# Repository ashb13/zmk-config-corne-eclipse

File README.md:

README | [Keymap](KEYMAP.md) | [MX Parts](PARTS_MX.md) | [Building](BUILDING.md) | [Tricks](TRICKS.md)

# Corne Eclipse

---

The Corne Eclipse is a highly customized wireless Corne MX.

*This was a project I initially finished in 2021. Finally updated and open sourced!*

## Custom Circuit Board Design

- JST port with line passthrough for undercarriage battery storage
- Native support for dual nice!view displays
- Native support for dual Alps EC11/EC12 encoders
- Native support for heftier side mounted power switches
- Native support for tenting puck

## Custom Shield Casing Design

Based on Void's case.

- Undercarriage battery storage
- Optimized material usage for bottom
- Native support for tenting puck

## Peripheral-side Trackpad Support

- TPS43 (and related Azoteq IQS5xx modules) via [AYM1607/zmk-driver-azoteq-iqs5xx](https://github.com/AYM1607/zmk-driver-azoteq-iqs5xx)
- Cirque Touchpad via [petejohanson/cirque-input-module](https://github.com/petejohanson/cirque-input-module)

## ZMK Modifications

### External Display Upgrades

- Lithium curve LUT applied for a 403450 to get more accurate numeric charge data (PR reference: [ZMK PR 2066](https://github.com/zmkfirmware/zmk/pull/2066))
- Track battery status of both halves on a single nice!view
- Capslock indicator

### RGB Battery Optimizations

Powered by [zmk-ext-power-smart-idle](https://github.com/Frosthaven/zmk-ext-power-smart-idle).

- 20% brightness when not plugged in
- RGB auto-off on low battery when not plugged in
- Lights stay on when plugged in
- Eclipse v3 reversible variant uses a MOSFET that prevents drain when LEDs are off (coming soon)

## Default Typing Layouts

Available in [releases](https://github.com/ashb13/zmk-config-corne-eclipse/releases).

- QWERTY
- Colemak Mod DH (personal choice!)
- Colemak
- Workman
- DVORAK

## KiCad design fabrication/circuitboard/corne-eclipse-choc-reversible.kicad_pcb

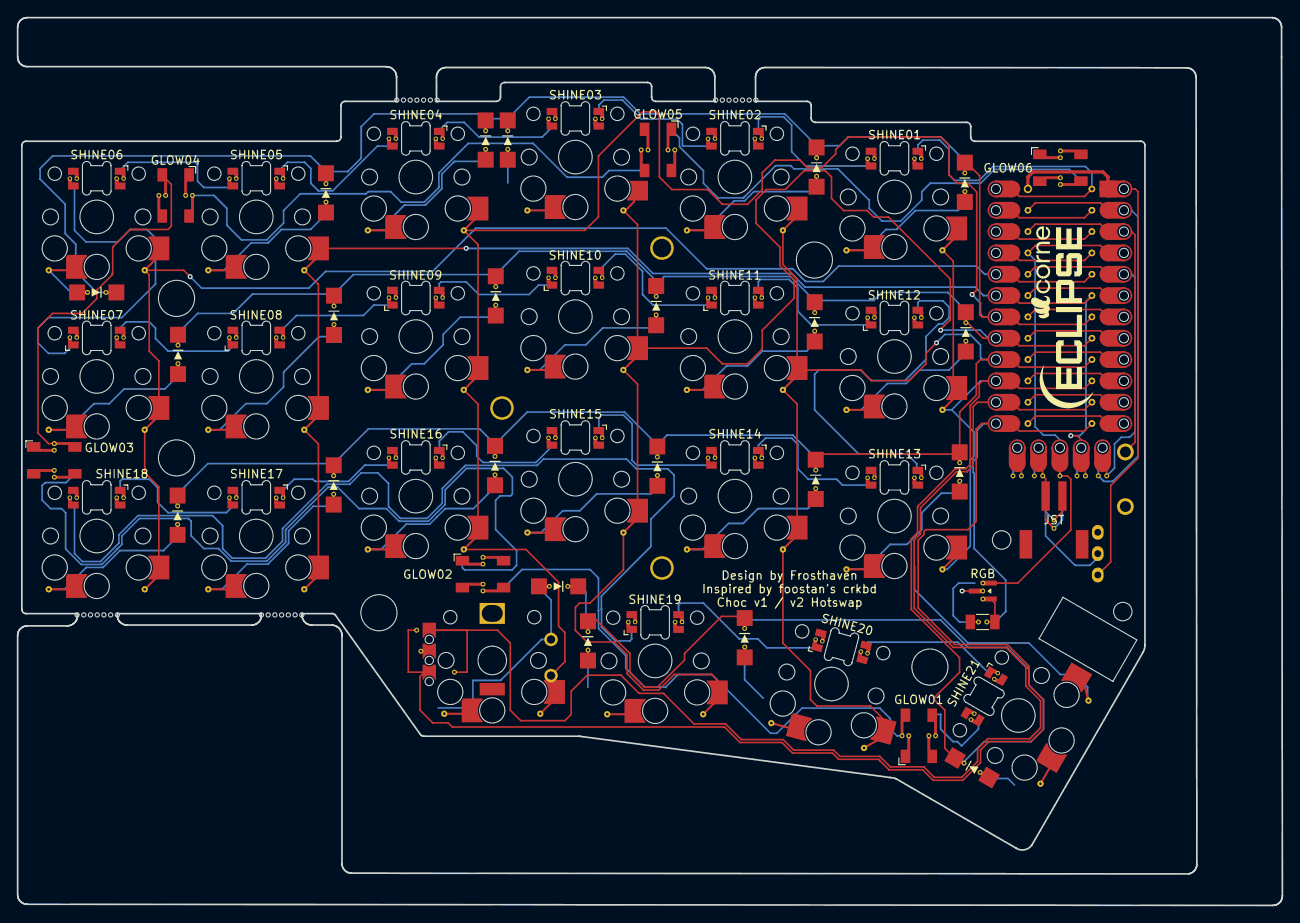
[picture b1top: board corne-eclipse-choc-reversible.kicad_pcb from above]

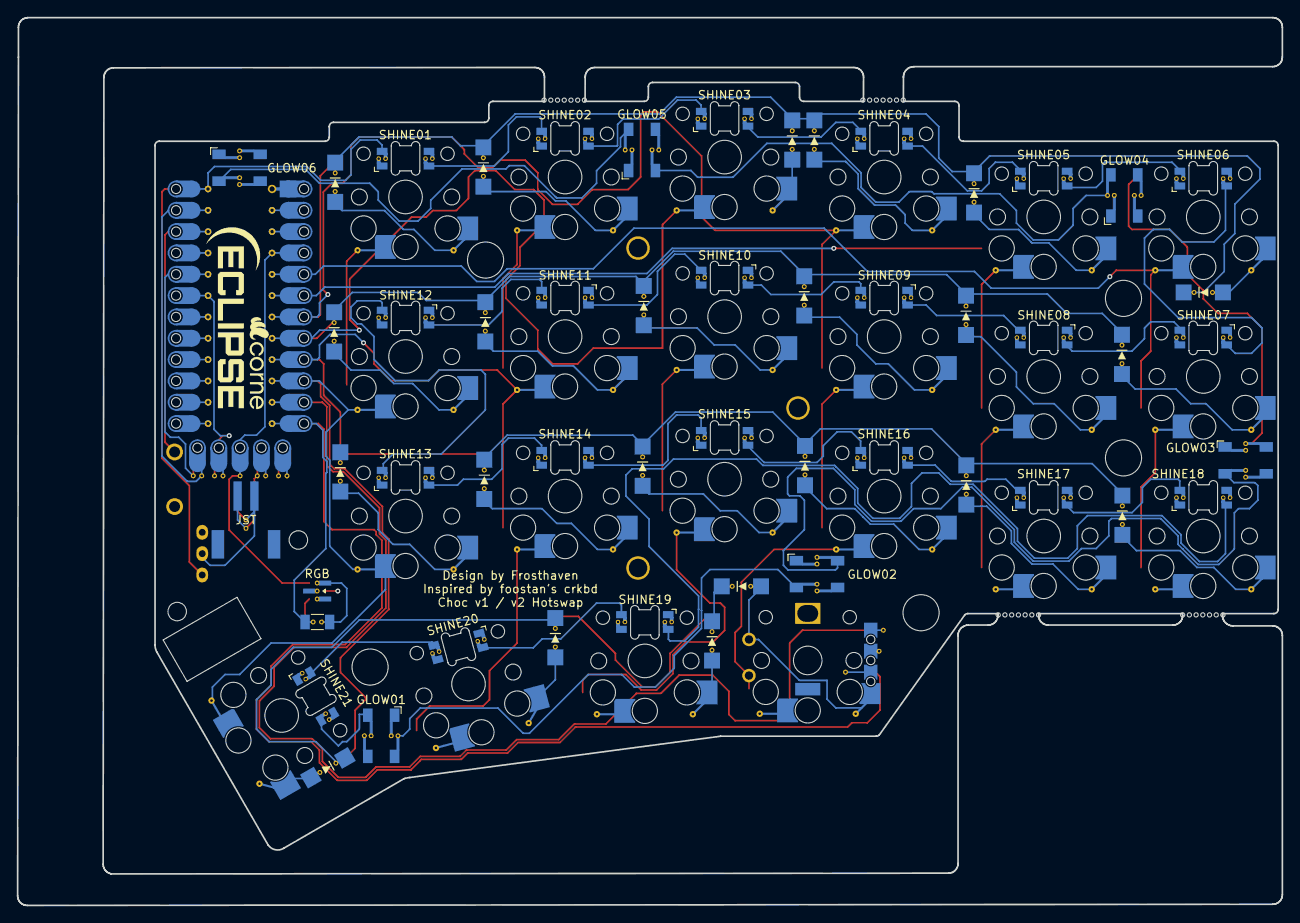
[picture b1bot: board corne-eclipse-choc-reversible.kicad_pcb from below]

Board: 4 copper layers, 150.6 x 105.7 mm, 91 parts (51 on the bottom side), 71 nets.

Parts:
BT1, BT2, BT3, BT4: Breakaway_Tabs
D1, D2, D3, D4, D5, D6, D7, D8, D9, D10, D11, D12, D13, D14, D15, D16, D17, D18, D19, D19B, D20, D21: D; ComboDiode-reversible
ENC1: ENC_SW_EC12_Choc; ENC_SW_EC12_Choc-reversible
GLOW01, GLOW02, GLOW03, GLOW04, GLOW05, GLOW06: WS2812B; SK6812_5050-reversible
J2: OLED; niceview-reversible
JPT1: JST Passthrough
JST: JST_PH-reversible
MH1, MH2, MH3, MH4, MH5, MH10, MH11: Val**; M2_HOLE_v2
PWR1: PowerSW-reversible
R1: 10k; R_1206-reversible
RGBMOS: AO3401A; SOT-23-reversible
RSW1: SW_PUSH; ResetSW-reversible
SHINE01, SHINE02, SHINE03, SHINE04, SHINE05, SHINE06, SHINE07, SHINE08, SHINE09, SHINE10, SHINE11, SHINE12, SHINE13, SHINE14, SHINE15, SHINE16, SHINE17, SHINE18, SHINE19, SHINE20, SHINE21: LED_6028R; SK6812_mini_e-reversible
SW1, SW2, SW3, SW4, SW5, SW6, SW7, SW8, SW9, SW10, SW11, SW12, SW13, SW14, SW15, SW16, SW17, SW18, SW20, SW21, SW22: SW_Choc_v1v2_HS; Choc_Hotswap-reversible
TP2: Tenting Puck; Tenting_Puck-reversible
U1: nice!nano; ProMicro-reversible

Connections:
BAT+: JST.2, PWR1.2
COL0: SW1.1, SW7.1, SW13.1, U1.20
COL1: SW2.1, SW8.1, SW14.1, U1.19
COL2: ENC1.1, ENC1.S2, SW3.1, SW9.1, SW15.1, U1.18
COL3: SW4.1, SW10.1, SW16.1, SW20.1, U1.17
COL4: SW5.1, SW11.1, SW17.1, SW21.1, U1.16
COL5: SW6.1, SW12.1, SW18.1, SW22.1, U1.15
ENC_A: ENC1.B, U1.11
ENC_B: ENC1.A, U1.12
EXT_PWR: R1.1, RGBMOS.2, U1.13
GND: ENC1.C, GLOW01.3, GLOW02.3, GLOW03.3, GLOW04.3, GLOW05.3, GLOW06.3, J2.4, JST.1, RSW1.2, SHINE01.3, SHINE02.3, SHINE03.3, SHINE04.3, SHINE05.3, SHINE06.3, SHINE07.3, SHINE08.3, SHINE09.3, SHINE10.3, SHINE11.3, SHINE12.3, SHINE13.3, SHINE14.3, SHINE15.3, SHINE16.3, SHINE17.3, SHINE18.3, SHINE19.3, SHINE20.3, SHINE21.3, TP2.1, U1.3, U1.4, U1.23
LED_CHAIN: SHINE01.4, U1.1
LED_PWR: GLOW01.1, GLOW02.1, GLOW03.1, GLOW04.1, GLOW05.1, GLOW06.1, RGBMOS.3, SHINE01.1, SHINE02.1, SHINE03.1, SHINE04.1, SHINE05.1, SHINE06.1, SHINE07.1, SHINE08.1, SHINE09.1, SHINE10.1, SHINE11.1, SHINE12.1, SHINE13.1, SHINE14.1, SHINE15.1, SHINE16.1, SHINE17.1, SHINE18.1, SHINE19.1, SHINE20.1, SHINE21.1
unnamed: D1.2, SW1.2
unnamed: D2.2, SW2.2
unnamed: D3.2, SW3.2
unnamed: D4.2, SW4.2
unnamed: D5.2, SW5.2
unnamed: D6.2, SW6.2
unnamed: D7.2, SW7.2
unnamed: D8.2, SW8.2
unnamed: D9.2, SW9.2
unnamed: D10.2, SW10.2
unnamed: D11.2, SW11.2
unnamed: D12.2, SW12.2
unnamed: D13.2, SW13.2
unnamed: D14.2, SW14.2
unnamed: D15.2, SW15.2
unnamed: D16.2, SW16.2
unnamed: D17.2, SW17.2
unnamed: D18.2, SW18.2
unnamed: D19B.2, ENC1.2, ENC1.S1
unnamed: D19.2, SW20.2
unnamed: D20.2, SW21.2
unnamed: D21.2, SW22.2
RAW: PWR1.1, U1.24
RESET: RSW1.1, U1.22
ROW1: D1.1, D2.1, D3.1, D4.1, D5.1, D6.1, U1.7
ROW2: D7.1, D8.1, D9.1, D10.1, D11.1, D12.1, U1.8
ROW3: D13.1, D14.1, D15.1, D16.1, D17.1, D18.1, U1.9
ROW4: D19.1, D19B.1, D20.1, D21.1, U1.10
VCC: J2.3, R1.2, RGBMOS.1, U1.21
VIEW_CS: J2.5, U1.2
VIEW_MOSI: J2.1, U1.5
VIEW_SCK: J2.2, U1.6
led1-led2: SHINE01.2, SHINE02.4
led2-led3: SHINE02.2, SHINE03.4
led3-led4: SHINE03.2, SHINE04.4
led4-led5: SHINE04.2, SHINE05.4
led5-led6: SHINE05.2, SHINE06.4
led6-led7: SHINE06.2, SHINE07.4
led7-led8: SHINE07.2, SHINE08.4
led8-led9: SHINE08.2, SHINE09.4
led9-led10: SHINE09.2, SHINE10.4
led10-led11: SHINE10.2, SHINE11.4
led11-led12: SHINE11.2, SHINE12.4
led12-led13: SHINE12.2, SHINE13.4
led13-led14: SHINE13.2, SHINE14.4
led14-led15: SHINE14.2, SHINE15.4
led15-led16: SHINE15.2, SHINE16.4
led16-led17: SHINE16.2, SHINE17.4
led17-led18: SHINE17.2, SHINE18.4
led18-led19: SHINE18.2, SHINE19.4
led19-led20: SHINE19.2, SHINE20.4
led20-led21: SHINE20.2, SHINE21.4
led21-led23: GLOW01.4, SHINE21.2
led23-led24: GLOW01.2, GLOW02.4
led24-led25: GLOW02.2, GLOW03.4
led25-led26: GLOW03.2, GLOW04.4
led26-led27: GLOW04.2, GLOW05.4
led27-led28: GLOW05.2, GLOW06.4

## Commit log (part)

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2026-03-30 Import Project
2026-03-31 fix(images): fixed label on `MSESYM` hotkey
2026-04-03 feat(mouse scroll): increase horizontal step from 25 -> 40
2026-04-03 chore(assets): match new mouse scroll bindings
2026-04-03 feat(encoder): make horizontal scroll step 75
2026-04-05 feat(rgb): prep for rgb configuration (mosfet gated)
2026-04-05 wip: v3 mx+choc variants
2026-04-05 feat: auto-off LEDs on idle
2026-04-05 chore: rename smart idle module to zmk-ext-power-smart-idle
2026-04-05 fix: DEVSYM encoder should use vertical scroll
2026-04-05 chore: update draft release with both keymap image links
2026-04-05 docs: rename Parts to MX Parts, merge Fabrication into it
2026-04-05 chore: gitignore lock files
2026-04-05 wip: logos, silkscreen cleanup, choc shield STLs, diode alignment
2026-04-06 chore: gitignore .blend1 backup files
2026-04-08 feat(case): more rounded edges instead of sharp for lp case
2026-04-08 wip(pcb): better alignment of components on choc pcb
2026-04-08 wip: rgb/choc
2026-04-08 fix(pcbs): aligned screw holes on lp and mx
2026-04-09 feat(pcb): wiring ready
2026-04-09 wip:pcbs
2026-04-09 feat(pcb): split mx design into north-facing and south-facing
2026-04-10 wip(pcbs): set board thicknesses
2026-04-10 feat(pcbs): finished ground and led power planes on all 3
2026-04-12 wip(pcbs): pre-validation
2026-04-14 wip(pcbs): reversible
2026-04-15 wip(pcbs): reversible footprints and choc progress
2026-04-15 wip(knobs): updating knob wall thickness
2026-04-16 wip(pcbs): fix invalid outline
2026-04-16 wip(pcbs): wiring
2026-04-16 feat(pcb): choc reversible fab-ready
2026-04-19 wip(choc): open and closed acrylic cases
2026-04-20 feat(encoders): reversed polarity of encoders for replacement parts
2026-04-20 fix(build): enable all typing options
2026-04-20 fix(build): default typing layers
2026-04-20 feat(rgb): cap max brightness at 50%
2026-04-20 Enable low battery LED cutoff at 2%
2026-04-20 Add CONFIG_ZMK_BATTERY for battery cutoff feature
2026-04-21 feat(trackpad): preliminary TPS43 firmware support for right side
2026-04-21 revert: restore scroll tap-ms to 100
2026-04-22 docs(parts): correct MX standoffs to 4mm with updated link
2026-04-22 build: sync build.yaml from upstream
    Pulls in upstream's full build matrix (Colemak-DH, Dvorak, plus
    trackpad variants for the right half). Ashley's prior "only build
    qwerty" customization is dropped.
2026-04-22 docs(readme): add TPS43 trackpad driver link
2026-04-22 feat(trackpad): add Cirque Pinnacle as an alternative to the TPS43
    TPS43 went EOL in April 2024 (Azoteq notice); Cirque GlidePoint Pinnacle
    is actively produced and is the recommended trackpad for new builds.
    - west.yml: pull in petejohanson/cirque-input-module.
    - right.overlay: split the single USE_TRACKPAD macro into two explicit
    variants (USE_TRACKPAD_TPS43, USE_TRACKPAD_CIRQUE). Legacy plain
    USE_TRACKPAD is aliased to USE_TRACKPAD_TPS43 for backward compat.
2026-04-23 feat(encoders): reverse encoder directions for replacement parts
    Volume up/down and mouse scroll up/down are reversed on this hardware.
    Also point the releases link at the ashb13 fork.
2026-04-26 chore(pcb): adjusted panel values
2026-04-26 fix(pcb): rename nets to match canonical nice!nano pinout (LED_CHAIN, VIEW_*, ROW1-4, COL0-5, ENC_A/B, BAT+)
2026-04-26 fix(pcb): rename Net-(U1-Pad24) to RAW (post-switch/diode rail to MCU)
2026-04-27 feat(keymap): change F13/F14/F15 to F16/F17/F18 on utility layer
2026-04-30 refactor(build): rename tps43 artifacts to azoteq for IQS5xx family
2026-04-30 fix(nice!view): center bullseye dot in profile circle outline
    Switch the assigned-profile outline from lv_canvas_draw_arc (which has
    Bresenham asymmetry at even radii, biasing the rendered pixels toward
    top-left of (cx,cy) and making the 3x3 dot appear shifted bottom-right)
    to lv_canvas_draw_rect with LV_RADIUS_CIRCLE. The rect-with-circle-radius
    gives a symmetric 1-pixel outline of diameter 2*r+1 = 13, so the visual
    center sits exactly on (cx,cy) and the bullseye dot is centered.
2026-05-02 fix(encoder): better manufacturing tolerances
2026-05-02 fix(encoder): more manufacturing tolerances
2026-05-04 wip(encoder): new design wip
2026-05-04 fix(encoder): object unit scale fix
2026-05-14 fix(overlay): delete nice!nano stock EXT_POWER node to resolve duplicate ext-power-generic instance
    nice!nano's base DTS defines /EXT_POWER (P0.13) as a convenience for
    boards whose MOSFET gate sits on the default pin. Our gate is on P0.10
    via /ext-power, but both nodes had compatible 'zmk,ext-power-generic'
    and their DT symbols collided to the same identifier (DT_N_S_ext_power).
    Zephyr generated two instances pointing at the same symbol, leaving
    instance 0's control-gpios config undefined and the driver unable to
2026-05-14 fix(overlay): correct ext-power control pin from P0.10 to P0.09
    ProMicro pad 13 (where the MOSFET gate is wired) maps to P0.09 / D10 on
    nice!nano v2, not P0.10. The wrong pin meant the driver was happily
    flipping P0.10 (which is actually SPI_SCK on pad 14) low at boot while
    the real MOSFET gate stayed pulled up to BAT+ via R1 — LEDs were never
    getting power.
    Fixed by changing control-gpios from <&gpio0 10 ...> to <&gpio0 9 ...>.
2026-05-15 fix(pcb): correct MOSFET and GLOW03 net assignments
    Two unrelated net-swap bugs in the choc-reversible PCB, both fixed by
    swapping net metadata and re-routing traces:
    1. SOT-23-reversible footprint (RGBMOS) had Pad 1 and Pad 2 net
    assignments inverted vs. the standard AO3401A pinout, so Gate ended
    up on BAT+ and Source on EXT_PWR (P-FET never switched). Swapped
    Pad 1 → BAT+, Pad 2 → EXT_PWR.
2026-05-15 feat(build): add dev_rgb_test variant with RGB enabled at boot
    Useful during assembly to verify the LED chain works before you have a
    working keymap with RGB_TOG available. QWERTY layout, both halves. Not
    intended for daily use. Flashing guide notes the recommended
    dev_rgb_test → settings_reset → daily flow.
2026-05-15 feat(conf): set USB-idle ext-power timeout to 2 hours
    Uses the new CONFIG_ZMK_EXT_POWER_SMART_IDLE_USB_TIMEOUT_S option from
    zmk-ext-power-smart-idle. After 2 hours of inactivity on USB, the LED
    rail will switch off. Restored on any keypress.
2026-05-15 build+conf+docs: bundle settings_reset in zips, revert USB timeout
    - Workflow: settings_reset.uf2 is now copied into each layout staging
    dir before zipping, so every layout zip includes it. Removed the
    standalone copy.
    - Conf: removed CONFIG_ZMK_EXT_POWER_SMART_IDLE_USB_TIMEOUT_S=7200
    because the smart-idle USB-timeout feature was reverted upstream
    (caused regression vs. local builds).
2026-05-15 fix(west): pin smart-idle to last known-good commit 6511488
    Cloud builds were pulling smart-idle@main HEAD which includes:
    - 74b251d: DT_NODELABEL -> DT_COMPAT lookup change
    - 1024e0d: ext_power_enable() at boot
    - 6e663b6: active_state_seen boot grace flag
    These together produce wrong RGB color (red instead of hue 220 blue)
    and break on-battery auto-off timeout. Pinning to 6511488 matches the
2026-05-15 chore(west): unpin smart-idle, return to main tracking
    Smart-idle main has been rebased to drop the buggy commits and now just
    has the clean USB timeout feature on top of 6511488. No pinning needed.
2026-05-15 fix(conf): move corne_eclipse.conf to config root so ZMK auto-loads it
    The shared shield conf was at config/boards/shields/corne_eclipse/
    corne_eclipse.conf — too deeply nested for ZMK's user-config flow to
    auto-load. Cloud builds were silently ignoring all the customization
    (HUE_START, BRT_START, SMART_IDLE settings, etc.) and using Kconfig
    defaults instead.
    Per ZMK docs: shared <shield>.conf is auto-loaded ONLY at
2026-05-15 fix(conf): remove undefined CONFIG_ZMK_EXT_POWER_START symbol
    This symbol doesn't exist in Kconfig. It was harmlessly ignored when
    corne_eclipse.conf wasn't being loaded (the bug we just fixed), but
    now that the conf is at the right path and gets auto-loaded, the
    undefined-symbol warning is fatal under Zephyr's strict mode.
    The behaviour this was trying to express (ext-power off at boot
    unless user toggles RGB on) is the default ZMK behaviour anyway —
2026-05-15 feat(trackpad): consolidate variants and add left-half trackpad option
    Each layout zip now bundles four variants: default and trackpad for each
    half. The trackpad variant bundles both Azoteq IQS5xx and Cirque Pinnacle
    drivers and auto-detects whichever module is wired. Both halves now offer
    a trackpad option since the PCB is reversible.
    Encoder coexists with trackpad: the trackpad RDY/DR signal moved from the
    encoder pin to the SPI_SCK net (silkscreen pad 14 = D16 / P0.10), so the
2026-05-15 fix(conf): fade idle MOSFET cut over 1s instead of 2s
2026-05-15 feat(conf): enable cross-half smart-idle sync + continuous brightness cap
2026-05-15 feat(ashley): invert encoder polarity + point releases link at ashb13
    The encoder on ashley's build is wired with reversed a/b signals, so
    volume + scroll need their args swapped to feel "normal" to the user.
    Compensates in the keymap (scroll_vertical macro, scroll_horizontal
    macro, all 8 inc_dec_kp sensor-bindings) without touching the dtsi.
    Also updates the README releases link to point at the ashb13 fork's
    release page so users on this branch download the correct firmware.
2026-05-15 feat(ashley): invert encoder polarity for reversed a/b wiring
2026-05-19 feat(ashley): tap Command alone → launch Raycast + point install URL at ashb13
    Adds a fourth Karabiner rule group that turns the Command key into a
    Raycast launcher when tapped on its own (fires Control+Space). Holding
    Command continues to work as a normal modifier thanks to lazy: true on
    the to mapping, so Cmd+S etc. behave identically.
    Also updates the karabiner:// install URL in KEYMAP.md to pull the
    Omni-shortcuts JSON from ashb13's fork instead of Frosthaven's.
2026-05-24 feat(ashley): inverted encoder polarity + ashb13 install URL
    Ashley's v3-choc-mx mirrors Frosthaven's exactly except: reversed encoder a/b
    wiring (keymap sensor-bindings) and the install URL pointed at ashb13.
2026-05-25 fix(encoder): correct zoom direction (opposite of upstream)
    Upstream fixed its right-encoder zoom direction; this fork keeps the opposite
    (<&zoom_in>, <&zoom_out>) to match its reversed encoder polarity.
2026-05-25 fix(encoder): EC12 tuning steps=64 + T=20 (mirror upstream)
    Picks up upstream's EC12 encoder resolution tuning (steps=64,
    triggers-per-rotation=20, verified 1 activation per detent) while keeping this
    fork's inverted encoder polarity and ashb13 URLs.
2026-05-26 build(west): bump zmk to d5963f2 (smart-idle before input-split chars)
    Fixes central->peripheral idle-activity sync on trackpad-on-peripheral builds.
    The central previously never discovered the smart-idle write handle (it sat
    after the input-split characteristics, which the central's input-descriptor
    discovery doesn't continue past), so it silently skipped the cross-half wake
    write. The fork now orders the smart-idle characteristic before the input-split
    chars and records the write handle without subscribing to NOTIFY.
2026-05-27 feat(mouse): faster emulated cursor (max 1200, ramp over 500ms)
    Raise ZMK_POINTING_DEFAULT_MOVE_VAL 600 -> 1200 (top cursor speed) and set the
    &mmv behavior's time-to-max-speed-ms to 500 (default 300).
2026-06-15 feat(trackpad): slow Azoteq cursor 25% via cursor-scale-percent
    Bump azoteq fork to fe0acfd (adds cursor-scale-percent DT prop that scales
    REL_X/REL_Y by a percentage before reporting). Set cursor-scale-percent = <75>
    on the azoteq_tp node in both right and left overlays so the cursor reports
    75% of the chip's raw delta -- 25% slower than before, consistent across hosts.
2026-06-18 feat(trackpad): slow Azoteq cursor 50% (cursor-scale-percent 75 -> 50)
2026-06-18 feat(encoder): right encoder always scrolls (drop trackpad zoom mode)
    The right encoder previously emitted Ctrl+scroll on trackpad builds
    (via the zoom_encoder behavior and zoom_in/zoom_out macros) and
    plain scroll otherwise. With the trackpad's two-finger scroll
    covering the same gesture, the encoder doesn't need to double as a
    zoom wheel -- unify on scroll for all builds.
    Collapse the TRACKPAD_PERIPHERAL/CENTRAL conditional in the keymap;
